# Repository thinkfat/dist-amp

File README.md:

dist-amp
========

This repository contains a 10MHz Distribution Amplifier (4  channels). It's
use is mainly in electronics labs or ham radio shacks for distributing a 
10MHz frequency standard (GPSDO, Rb atomic clock).

The circuit is based on a design by W. H. Rech, DF9IC, with minor modifications
by myself.

Documenation
------------

The *doc* folder contains the schematic in PDF format. It also contains S11/S21 measurements
done with a NanoVNA V2plus4 (nanovna-saver screenshot):

- Maximum input: 10dBm into 50 Ohm
- Cut-off frequency (-3dB): 13.8MHz
- Roll-off: 38dB/octave
- S11 @ 10MHz: -27dB
- S21 @ 10MHz: -0.7dB

Switching the ports I got also:
- S12 @ 10MHz: < -90dB

  In other words, the VNA cannot measure it. The dynamic range is not big enough.

Fabrication
-----------

The *fab* folder contains Gerber plots, a drill file and CPL+BOM files for
JLCPCB SMT service. If you want to recreate the board, remember to enable
impedance control and choose the JLC7628 PCB stack-up.

BOM
---

The *bom* folder contains an interactive HTML BOM you can open in a browser. It will
help with sourcing parts and assembling the PCB. Most parts are generic, but some parts
must meet either footprint or electrical constraints.

- L1, L2: Johanson Technology L-15F1R0JV4E
- U2: Maxim MAX4022ESD+
- J6: CUI PJ-037BH
- C13-C15: use MLCC capacitors with C0G/NP0 dielectric

Customization
-------------

The MAX4022ESD+ has a much larger bandwidth than the 12MHz imposed by the input filter.
One obvious modification is therefore to choose a higher roll-off frequency for the
input low-pass. Note that total bandwidth and flatness will also depend on parameters
of other components in the signal path, notably coupling capacitors at in and output.
These are currently generic 100nF MLCC with X7R dielectric. For more demanding applications,
you might need to find better ones.

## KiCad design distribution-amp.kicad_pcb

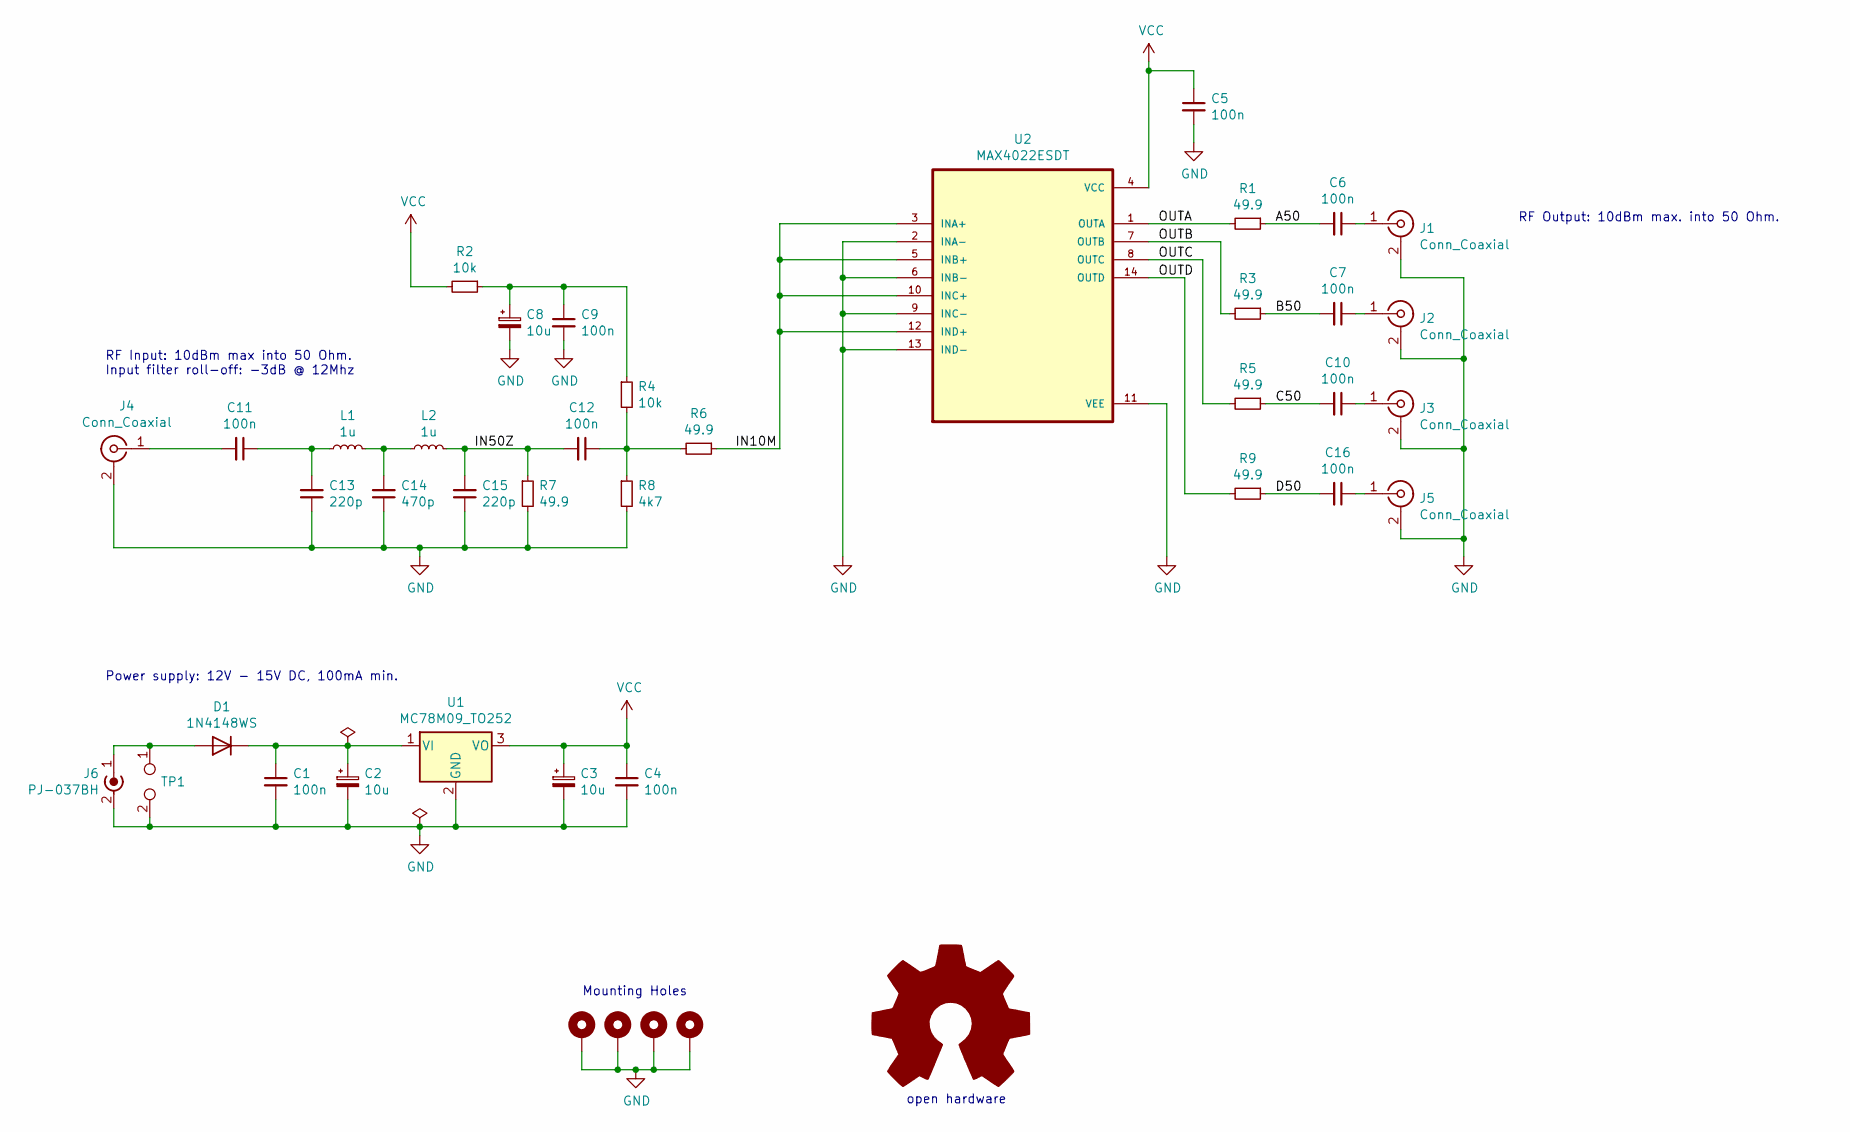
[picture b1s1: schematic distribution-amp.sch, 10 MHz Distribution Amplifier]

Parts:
C1, C4, C5, C6, C7, C9, C10, C11, C12, C16: 100n; C_0805_2012Metric_Pad1.18x1.45mm_HandSolder; LCSCPN C49678
C2, C3, C8: 10u; CP_Elec_5x5.4; LCSCPN C72487
C13, C15: 220p; C_0805_2012Metric_Pad1.18x1.45mm_HandSolder; LCSCPN C61747
C14: 470p; C_0805_2012Metric_Pad1.18x1.45mm_HandSolder; LCSCPN C28256
D1: 1N4148WS; D_SOD-323; LCSCPN C2128
H1, H2, H3, H4: MountingHole_Pad; MountingHole_3.2mm_M3_Pad_Via
J1, J2, J3, J4, J5: Conn_Coaxial; SMA_Amphenol_132203-12_Horizontal
J6: PJ-037BH; CUI_PJ-037BH
L1, L2: 1u; L_0805_2012Metric_Pad1.05x1.20mm_HandSolder
OSHW1: Logo_Open_Hardware_Large; OSHW-Logo2_14.6x12mm_Copper
R1, R3, R5, R6, R7, R9: 49.9; R_0805_2012Metric_Pad1.20x1.40mm_HandSolder; LCSCPN C17720
R2, R4: 10k; R_0805_2012Metric_Pad1.20x1.40mm_HandSolder; LCSCPN C17414
R8: 4k7; R_0805_2012Metric_Pad1.20x1.40mm_HandSolder; LCSCPN C17673
TP1: TestPoint_2Pole; PinHeader_1x02_P2.54mm_Vertical
U1: MC78M09_TO252; TO-252-2; LCSCPN C148310
U2: MAX4022ESDT; SOIC-14_3.9x8.7mm_P1.27mm

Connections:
/A50: C6.2, R1.1
/B50: C7.2, R3.1
/C50: C10.2, R5.1
/D50: C16.2, R9.1
/IN10M: R6.1, U2.3 (INA+), U2.5 (INB+), U2.10 (INC+), U2.12 (IND+)
/IN50Z: C12.2, C15.2, L2.2, R7.1
/OUTA: R1.2, U2.1 (OUTA)
/OUTB: R3.2, U2.7 (OUTB)
/OUTC: R5.2, U2.8 (OUTC)
/OUTD: R9.2, U2.14 (OUTD)
GND: C1.2, C2.2, C3.2, C4.2, C5.2, C8.2, C9.2, C13.1, C14.1, C15.1, H1.1, H2.1, H3.1, H4.1, J1.2 (Ext), J2.2 (Ext), J3.2 (Ext), J4.2 (Ext), J5.2 (Ext), J6.2 (Ext), R7.2, R8.2, TP1.2, U1.2 (GND), U2.2 (INA-), U2.6 (INB-), U2.9 (INC-), U2.11 (VEE), U2.13 (IND-)
unnamed: C1.1, C2.1, D1.1 (K), U1.1 (VI)
unnamed: C6.1, J1.1 (In)
unnamed: C7.1, J2.1 (In)
unnamed: C8.1, C9.1, R2.1, R4.1
unnamed: C10.1, J3.1 (In)
unnamed: C11.1, C13.2, L1.1
unnamed: C11.2, J4.1 (In)
unnamed: C12.1, R4.2, R6.2, R8.1
unnamed: C14.2, L1.2, L2.1
unnamed: C16.1, J5.1 (In)
unnamed: D1.2 (A), J6.1 (In), TP1.1
VCC: C3.1, C4.1, C5.1, R2.2, U1.3 (VO), U2.4 (VCC)

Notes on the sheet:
open hardware
Mounting Holes
Power supply: 12V - 15V DC, 100mA min.
RF Input: 10dBm max into 50 Ohm. Input filter roll-off: -3dB @ 12Mhz
RF Output: 10dBm max. into 50 Ohm.

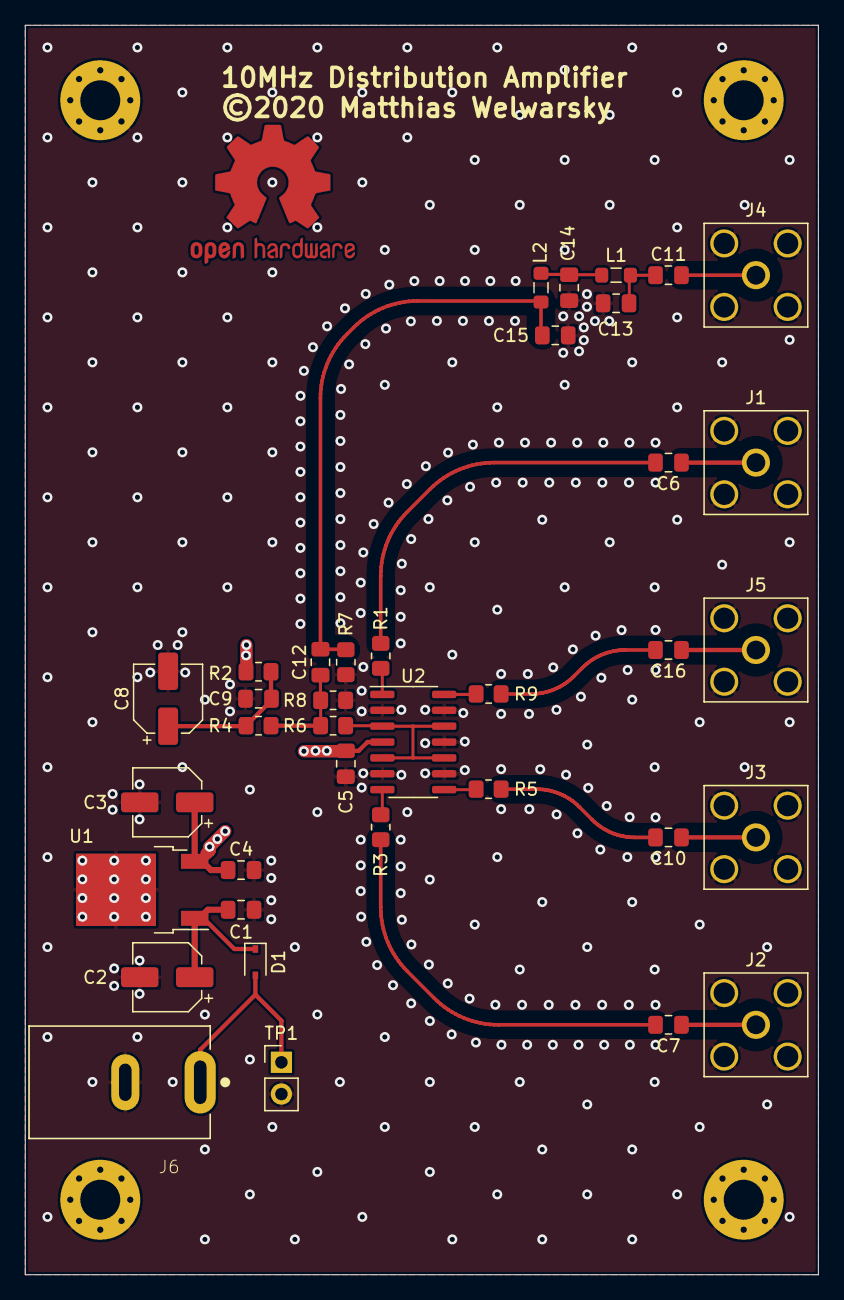
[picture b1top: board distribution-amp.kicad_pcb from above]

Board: 4 copper layers, 63.5 x 100.0 mm, 42 parts (0 on the bottom side), 23 nets.

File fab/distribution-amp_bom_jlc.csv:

"Comment","Designator","Footprint","LCSC Part #"
"10u","C8,C2,C3","CP_Elec_5x5.4","C72487"
"100n","C11,C6,C7,C10,C16,C4,C1,C9,C12,C5","C_0805_2012Metric_Pad1.18x1.45mm_HandSolder","C49678"
"220p","C13,C15","C_0805_2012Metric_Pad1.18x1.45mm_HandSolder","C61747"
"470p","C14","C_0805_2012Metric_Pad1.18x1.45mm_HandSolder","C28256"
"1N4148WS","D1","D_SOD-323","C2128"
"49.9","R1,R3,R5,R9,R7,R6","R_0805_2012Metric_Pad1.20x1.40mm_HandSolder","C17720"
"10k","R4,R2","R_0805_2012Metric_Pad1.20x1.40mm_HandSolder","C17414"
"4k7","R8","R_0805_2012Metric_Pad1.20x1.40mm_HandSolder","C17673"
"MC78M09_TO252","U1","TO-252-2","C148310"

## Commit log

2021-01-09 Add documentation
2021-01-09 add amplifier analysis (NanoVNA V2+4)
2021-01-09 Update analysis.png after VNA recalibration
2021-01-09 Documentation update

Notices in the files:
distribution-amp.kicad_pcb:
©2020 Matthias Welwarsky
